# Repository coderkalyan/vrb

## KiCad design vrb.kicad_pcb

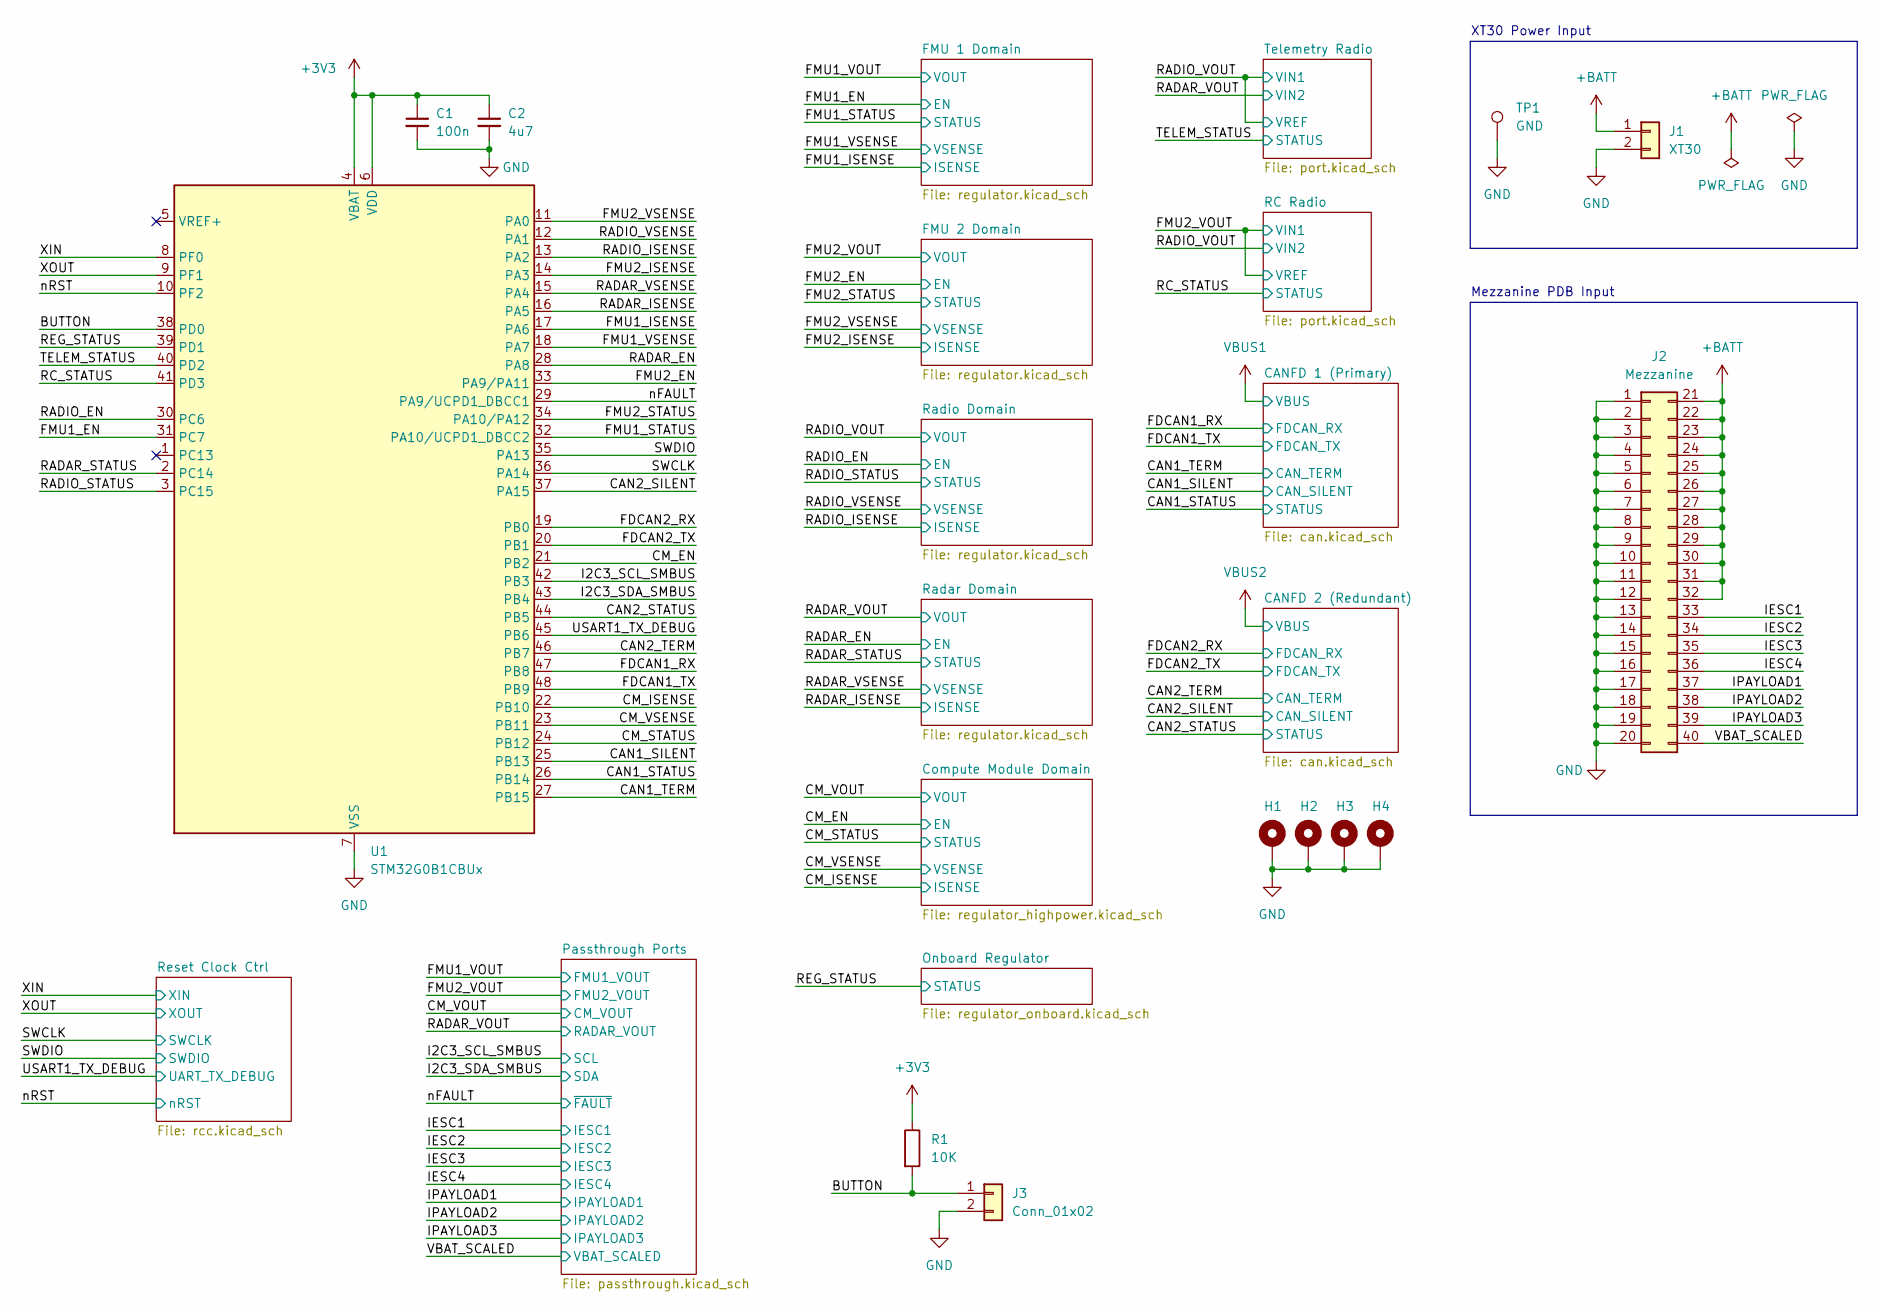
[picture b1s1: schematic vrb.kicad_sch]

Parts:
C1: 100n; C_0402_1005Metric
C2: 4u7; C_0402_1005Metric
H1, H2, H3, H4: MountingHole_Pad; MountingHole_3.2mm_M3_Pad_Via
J1: XT30; AMASS_XT30PW-M_1x02_P2.50mm_Horizontal
J2: Mezzanine; CON_528850474_MOL
J3: Conn_01x02; PinHeader_1x02_P2.54mm_Vertical
R1: 10K; R_0402_1005Metric
TP1: GND; TestPoint_Loop_D2.50mm_Drill1.0mm
U1: STM32G0B1CBUx; QFN-48-1EP_7x7mm_P0.5mm_EP5.6x5.6mm

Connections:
+3V3: C1.1, C2.1, R1.1, U1.4 (VBAT), U1.6 (VDD); also elsewhere on the board
+BATT: J1.1, J2.21, J2.22, J2.23, J2.24, J2.25, J2.26, J2.27, J2.28, J2.29, J2.30, J2.31, J2.32; also elsewhere on the board
/BUTTON: J3.1, R1.2, U1.38 (PD0)
/CAN1_SILENT: U1.25 (PB13); also elsewhere on the board
/CAN1_STATUS: U1.26 (PB14); also elsewhere on the board
/CAN1_TERM: U1.27 (PB15); also elsewhere on the board
/CAN2_SILENT: U1.37 (PA15); also elsewhere on the board
/CAN2_STATUS: U1.44 (PB5); also elsewhere on the board
/CAN2_TERM: U1.46 (PB7); also elsewhere on the board
/CM_EN: U1.21 (PB2); also elsewhere on the board
/CM_ISENSE: U1.22 (PB10); also elsewhere on the board
/CM_STATUS: U1.24 (PB12); also elsewhere on the board
/CM_VSENSE: U1.23 (PB11); also elsewhere on the board
/FDCAN1_RX: U1.47 (PB8); also elsewhere on the board
/FDCAN1_TX: U1.48 (PB9); also elsewhere on the board
/FDCAN2_RX: U1.19 (PB0); also elsewhere on the board
/FDCAN2_TX: U1.20 (PB1); also elsewhere on the board
/FMU1_EN: U1.31 (PC7); also elsewhere on the board
/FMU1_ISENSE: U1.17 (PA6); also elsewhere on the board
/FMU1_STATUS: U1.32 (PA10/UCPD1_DBCC2); also elsewhere on the board
/FMU1_VSENSE: U1.18 (PA7); also elsewhere on the board
/FMU2_EN: U1.33 (PA9/PA11); also elsewhere on the board
/FMU2_ISENSE: U1.14 (PA3); also elsewhere on the board
/FMU2_STATUS: U1.34 (PA10/PA12); also elsewhere on the board
/FMU2_VSENSE: U1.11 (PA0); also elsewhere on the board
/I2C3_SCL_SMBUS: U1.42 (PB3); also elsewhere on the board
/I2C3_SDA_SMBUS: U1.43 (PB4); also elsewhere on the board
/IESC1: J2.33; also elsewhere on the board
/IESC2: J2.34; also elsewhere on the board
/IESC3: J2.35; also elsewhere on the board
/IESC4: J2.36; also elsewhere on the board
/IPAYLOAD1: J2.37; also elsewhere on the board
/IPAYLOAD2: J2.38; also elsewhere on the board
/IPAYLOAD3: J2.39; also elsewhere on the board
/RADAR_EN: U1.28 (PA8); also elsewhere on the board
/RADAR_ISENSE: U1.16 (PA5); also elsewhere on the board
/RADAR_STATUS: U1.2 (PC14); also elsewhere on the board
/RADAR_VSENSE: U1.15 (PA4); also elsewhere on the board
/RADIO_EN: U1.30 (PC6); also elsewhere on the board
/RADIO_ISENSE: U1.13 (PA2); also elsewhere on the board
/RADIO_STATUS: U1.3 (PC15); also elsewhere on the board
/RADIO_VSENSE: U1.12 (PA1); also elsewhere on the board
/RC_STATUS: U1.41 (PD3); also elsewhere on the board
/REG_STATUS: U1.39 (PD1); also elsewhere on the board
/SWCLK: U1.36 (PA14); also elsewhere on the board
/SWDIO: U1.35 (PA13); also elsewhere on the board
/TELEM_STATUS: U1.40 (PD2); also elsewhere on the board
/USART1_TX_DEBUG: U1.45 (PB6); also elsewhere on the board
/VBAT_SCALED: J2.40; also elsewhere on the board
/XIN: U1.8 (PF0); also elsewhere on the board
/XOUT: U1.9 (PF1); also elsewhere on the board
/nFAULT: U1.29 (PA9/UCPD1_DBCC1); also elsewhere on the board
/nRST: U1.10 (PF2); also elsewhere on the board
GND: C1.2, C2.2, H1.1, H2.1, H3.1, H4.1, J1.2, J2.1, J2.2, J2.3, J2.4, J2.5, J2.6, J2.7, J2.8, J2.9, J2.10, J2.11, J2.12, J2.13, J2.14, J2.15, J2.16, J2.17, J2.18, J2.19, J2.20, J3.2, TP1.1, U1.7 (VSS), U1.49 (VSS); also elsewhere on the board

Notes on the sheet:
XT30 Power Input
Mezzanine PDB Input

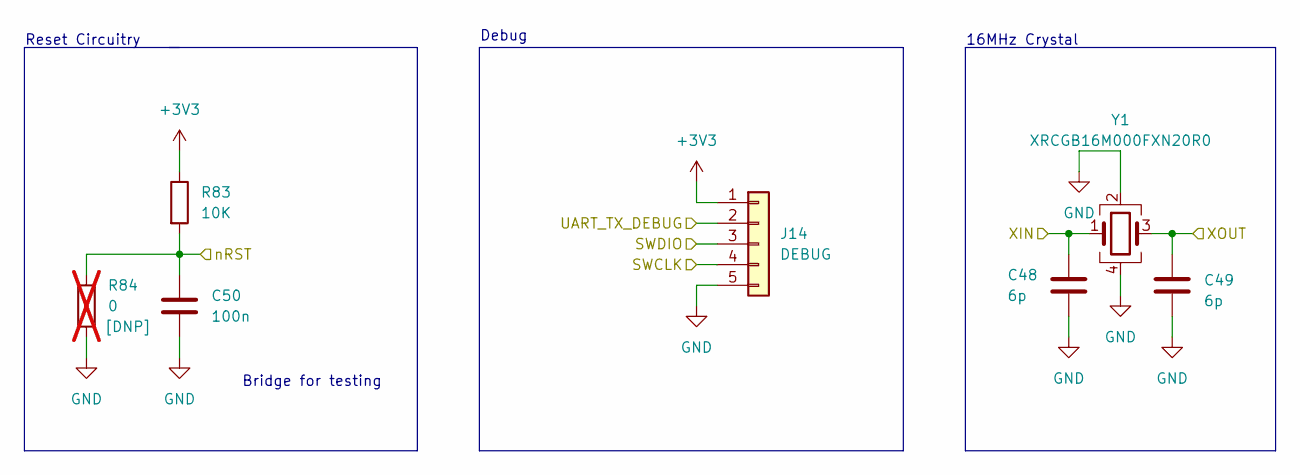
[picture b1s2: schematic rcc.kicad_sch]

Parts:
C48, C49: 6p; C_0402_1005Metric; LCSC C466231
C50: 100n; C_0402_1005Metric; LCSC C907967
J14: DEBUG; PinHeader_1x05_P2.54mm_Vertical
R83: 10K; R_0402_1005Metric; LCSC C102690
R84: 0; R_0402_1005Metric; not fitted
Y1: XRCGB16M000FXN20R0; Crystal_SMD_2016-4Pin_2.0x1.6mm; Part XRCGB16M000FXN20R0; LCSC C907977

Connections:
+3V3: J14.1, R83.1; also elsewhere on the board
/SWCLK: J14.4; also elsewhere on the board
/SWDIO: J14.3; also elsewhere on the board
/USART1_TX_DEBUG: J14.2; also elsewhere on the board
/XIN: C48.1, Y1.1; also elsewhere on the board
/XOUT: C49.1, Y1.3; also elsewhere on the board
/nRST: C50.1, R83.2, R84.1; also elsewhere on the board
GND: C48.2, C49.2, C50.2, J14.5, R84.2, Y1.2, Y1.4; also elsewhere on the board

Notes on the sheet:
Reset Circuitry
Bridge for testing
16MHz Crystal
Debug

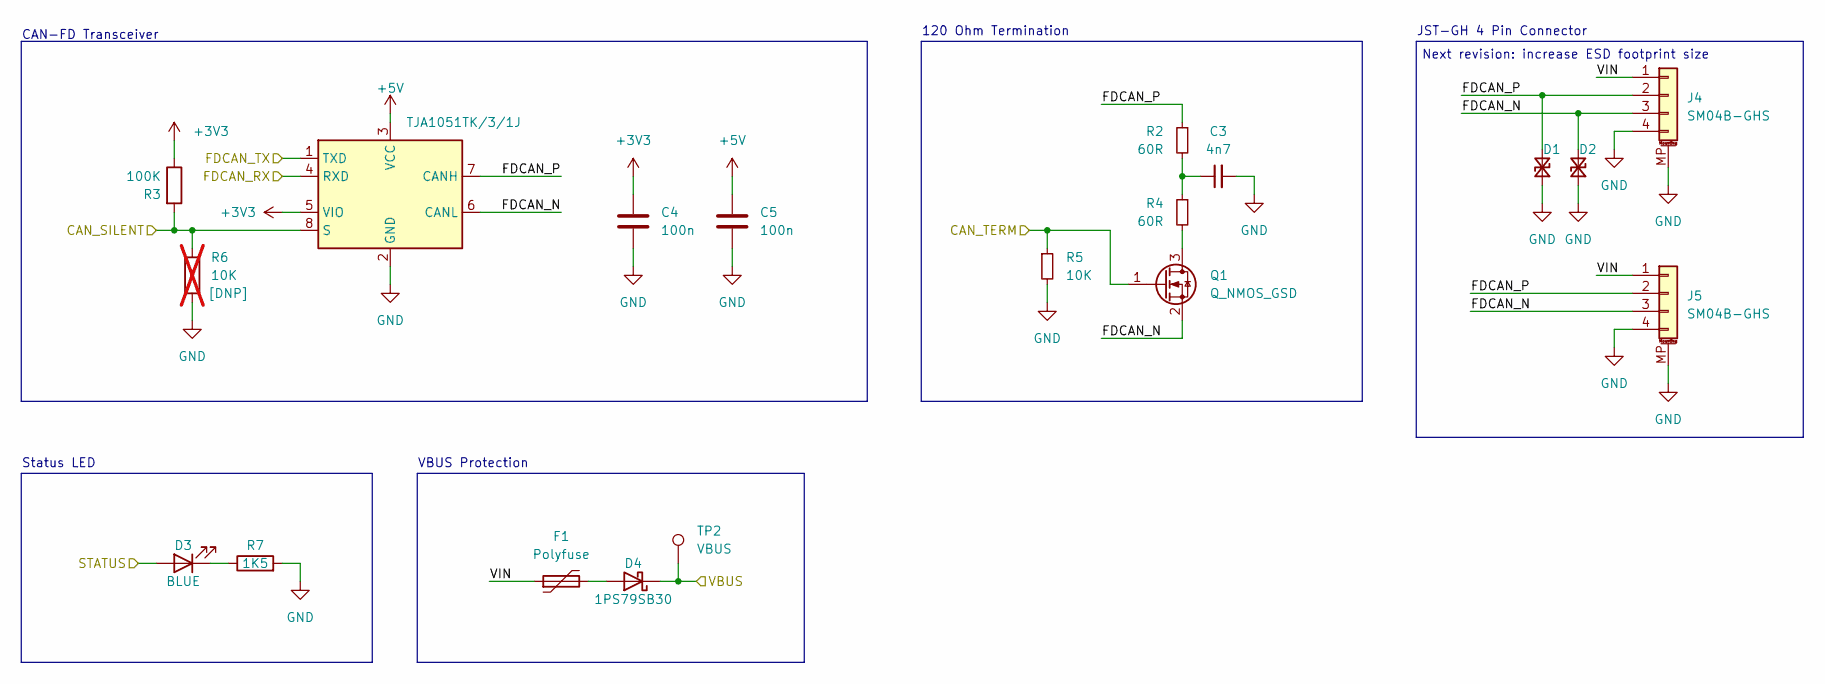
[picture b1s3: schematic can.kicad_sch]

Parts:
C3: 4n7; C_0402_1005Metric
C4, C5: 100n; C_0402_1005Metric
D1, D2: D_TVS_Small; Nexperia_DSN0603-2_0.6x0.3mm_P0.4mm
D3: BLUE; LED_0603_1608Metric
D4: 1PS79SB30; D_SOD-523; LCSC C426690
F1: Polyfuse; Fuse_1206_3216Metric
J4, J5: SM04B-GHS; JST_GH_SM04B-GHS-TB_1x04-1MP_P1.25mm_Horizontal
Q1: Q_NMOS_GSD; SOT-23-3
R2, R4: 60R; R_0402_1005Metric
R3: 100K; R_0402_1005Metric
R5: 10K; R_0402_1005Metric
R6: 10K; R_0402_1005Metric; not fitted
R7: 1K5; R_0402_1005Metric
TP2: VBUS; TestPoint_Pad_1.0x1.0mm
U2: TJA1051TK/3/1J; HVSON-8-1EP_3x3mm_P0.65mm_EP1.6x2.4mm

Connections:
+3V3: C4.1, R3.1, U2.5 (VIO); also elsewhere on the board
+5V: C5.1, U2.3 (VCC); also elsewhere on the board
/CAN2_SILENT: R3.2, R6.1, U2.8 (S); also elsewhere on the board
/CAN2_STATUS: D3.2 (A); also elsewhere on the board
/CAN2_TERM: Q1.1 (G), R5.1; also elsewhere on the board
/CANFD 2 (Redundant)/FDCAN_N: D2.2 (A2), J4.3, J5.3, Q1.2 (S), U2.6 (CANL)
/CANFD 2 (Redundant)/FDCAN_P: D1.2 (A2), J4.2, J5.2, R2.1, U2.7 (CANH)
/CANFD 2 (Redundant)/VIN: F1.1, J4.1, J5.1
/FDCAN2_RX: U2.4 (RXD); also elsewhere on the board
/FDCAN2_TX: U2.1 (TXD); also elsewhere on the board
GND: C3.2, C4.2, C5.2, D1.1 (A1), D2.1 (A1), J4.4, J4.MP (MountPin), J5.4, J5.MP (MountPin), R5.2, R6.2, R7.2, U2.2 (GND), U2.9 (GND); also elsewhere on the board
unnamed: C3.1, R2.2, R4.1
unnamed: D3.1 (K), R7.1
unnamed: D4.2 (A), F1.2
unnamed: Q1.3 (D), R4.2
VBUS2: D4.1 (K), TP2.1; also elsewhere on the board

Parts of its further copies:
C31: 4n7; C_0402_1005Metric
C32, C33: 100n; C_0402_1005Metric
D9, D10: D_TVS_Small; Nexperia_DSN0603-2_0.6x0.3mm_P0.4mm
D11: BLUE; LED_0603_1608Metric
D12: 1PS79SB30; D_SOD-523; LCSC C426690
F6: Polyfuse; Fuse_1206_3216Metric
J6, J7: SM04B-GHS; JST_GH_SM04B-GHS-TB_1x04-1MP_P1.25mm_Horizontal
Q2: Q_NMOS_GSD; SOT-23-3
R40, R42: 60R; R_0402_1005Metric
R41: 100K; R_0402_1005Metric
R45: 10K; R_0402_1005Metric
R46: 10K; R_0402_1005Metric; not fitted
R49: 1K5; R_0402_1005Metric
TP7: VBUS; TestPoint_Pad_1.0x1.0mm
U11: TJA1051TK/3/1J; HVSON-8-1EP_3x3mm_P0.65mm_EP1.6x2.4mm

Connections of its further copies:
+3V3: C32.1, R41.1, U11.5 (VIO); also elsewhere on the board
+5V: C33.1, U11.3 (VCC); also elsewhere on the board
/CAN1_SILENT: R41.2, R46.1, U11.8 (S); also elsewhere on the board
/CAN1_STATUS: D11.2 (A); also elsewhere on the board
/CAN1_TERM: Q2.1 (G), R45.1; also elsewhere on the board
/CANFD 1 (Primary)/FDCAN_N: D10.2 (A2), J6.3, J7.3, Q2.2 (S), U11.6 (CANL)
/CANFD 1 (Primary)/FDCAN_P: D9.2 (A2), J6.2, J7.2, R40.1, U11.7 (CANH)
/CANFD 1 (Primary)/VIN: F6.1, J6.1, J7.1
/FDCAN1_RX: U11.4 (RXD); also elsewhere on the board
/FDCAN1_TX: U11.1 (TXD); also elsewhere on the board
GND: C31.2, C32.2, C33.2, D9.1 (A1), D10.1 (A1), J6.4, J6.MP (MountPin), J7.4, J7.MP (MountPin), R45.2, R46.2, R49.2, U11.2 (GND), U11.9 (GND); also elsewhere on the board
unnamed: C31.1, R40.2, R42.1
unnamed: D11.1 (K), R49.1
unnamed: D12.2 (A), F6.2
unnamed: Q2.3 (D), R42.2
VBUS1: D12.1 (K), TP7.1; also elsewhere on the board

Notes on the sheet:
CAN-FD Transceiver
Next revision: increase ESD footprint size
JST-GH 4 Pin Connector
Status LED
VBUS Protection
120 Ohm Termination

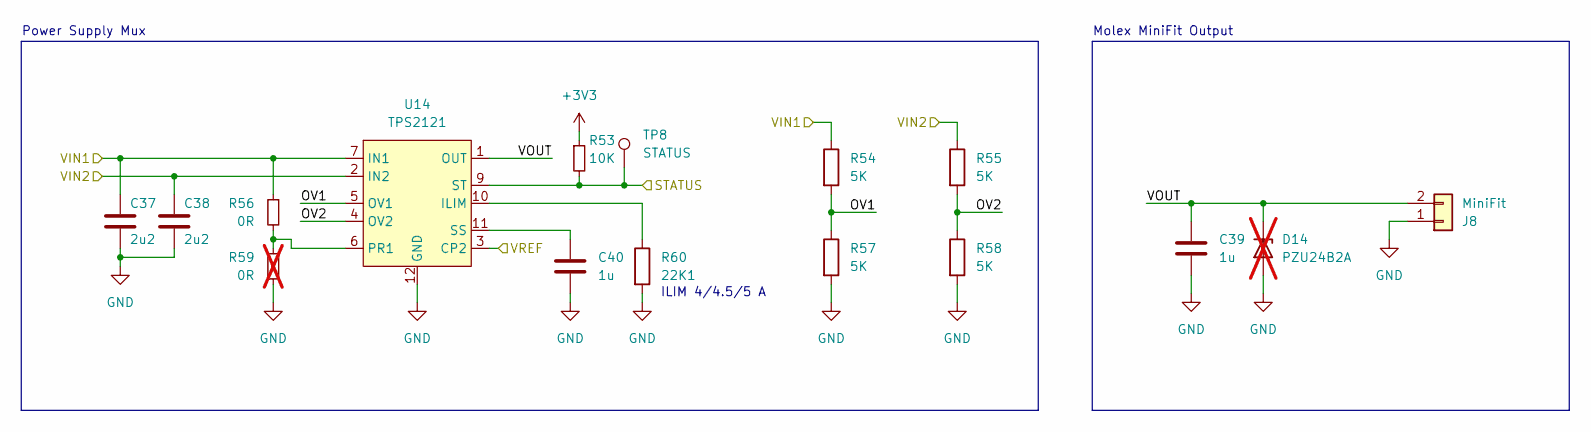
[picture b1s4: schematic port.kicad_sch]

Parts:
C37, C38: 2u2; C_0603_1608Metric
C39, C40: 1u; C_0603_1608Metric
D14: PZU24B2A; D_SOD-323F; not fitted
J8: MiniFit; Molex_Mini-Fit_Jr_5569-02A2_2x01_P4.20mm_Horizontal
R53: 10K; R_0402_1005Metric
R54, R55: 5K; R_0603_1608Metric
R56: 0R; R_0603_1608Metric
R57, R58: 5K; R_0402_1005Metric
R59: 0R; R_0402_1005Metric; not fitted
R60: 22K1; R_0603_1608Metric
TP8: STATUS; TestPoint_Pad_1.0x1.0mm
U14: TPS2121; Texas_VQFN-HR-12_2x2.5mm_P0.5mm

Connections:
+3V3: R53.1; also elsewhere on the board
/FMU2_VOUT: C37.1, R54.1, R56.1, U14.3 (CP2), U14.7 (IN1); also elsewhere on the board
/RADIO_VOUT: C38.1, R55.1, U14.2 (IN2); also elsewhere on the board
/RC Radio/OV1: R54.2, R57.1, U14.5 (OV1)
/RC Radio/OV2: R55.2, R58.1, U14.4 (OV2)
/RC Radio/VOUT: C39.1, D14.1 (K), J8.2, U14.1 (OUT), U14.8 (OUT)
/RC_STATUS: R53.2, TP8.1, U14.9 (ST); also elsewhere on the board
GND: C37.2, C38.2, C39.2, C40.2, D14.2 (A), J8.1, R57.2, R58.2, R59.2, R60.2, U14.12 (GND); also elsewhere on the board
unnamed: R60.1, U14.10 (ILIM)
unnamed: R56.2, R59.1, U14.6 (PR1)
unnamed: C40.1, U14.11 (SS)

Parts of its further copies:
C41, C42: 2u2; C_0603_1608Metric
C43, C44: 1u; C_0603_1608Metric
D15: PZU24B2A; D_SOD-323F; not fitted
J9: MiniFit; Molex_Mini-Fit_Jr_5569-02A2_2x01_P4.20mm_Horizontal
R61: 10K; R_0402_1005Metric
R62, R63: 5K; R_0603_1608Metric
R64: 0R; R_0603_1608Metric
R65, R66: 5K; R_0402_1005Metric
R67: 0R; R_0402_1005Metric; not fitted
R68: 22K1; R_0603_1608Metric
TP9: STATUS; TestPoint_Pad_1.0x1.0mm
U15: TPS2121; Texas_VQFN-HR-12_2x2.5mm_P0.5mm

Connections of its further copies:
+3V3: R61.1; also elsewhere on the board
/RADAR_VOUT: C42.1, R63.1, U15.2 (IN2); also elsewhere on the board
/RADIO_VOUT: C41.1, R62.1, R64.1, U15.3 (CP2), U15.7 (IN1); also elsewhere on the board
/TELEM_STATUS: R61.2, TP9.1, U15.9 (ST); also elsewhere on the board
/Telemetry Radio/OV1: R62.2, R65.1, U15.5 (OV1)
/Telemetry Radio/OV2: R63.2, R66.1, U15.4 (OV2)
/Telemetry Radio/VOUT: C43.1, D15.1 (K), J9.2, U15.1 (OUT), U15.8 (OUT)
GND: C41.2, C42.2, C43.2, C44.2, D15.2 (A), J9.1, R65.2, R66.2, R67.2, R68.2, U15.12 (GND); also elsewhere on the board
unnamed: R68.1, U15.10 (ILIM)
unnamed: R64.2, R67.1, U15.6 (PR1)
unnamed: C44.1, U15.11 (SS)

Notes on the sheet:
Molex MiniFit Output
Power Supply Mux
ILIM 4/4.5/5 A

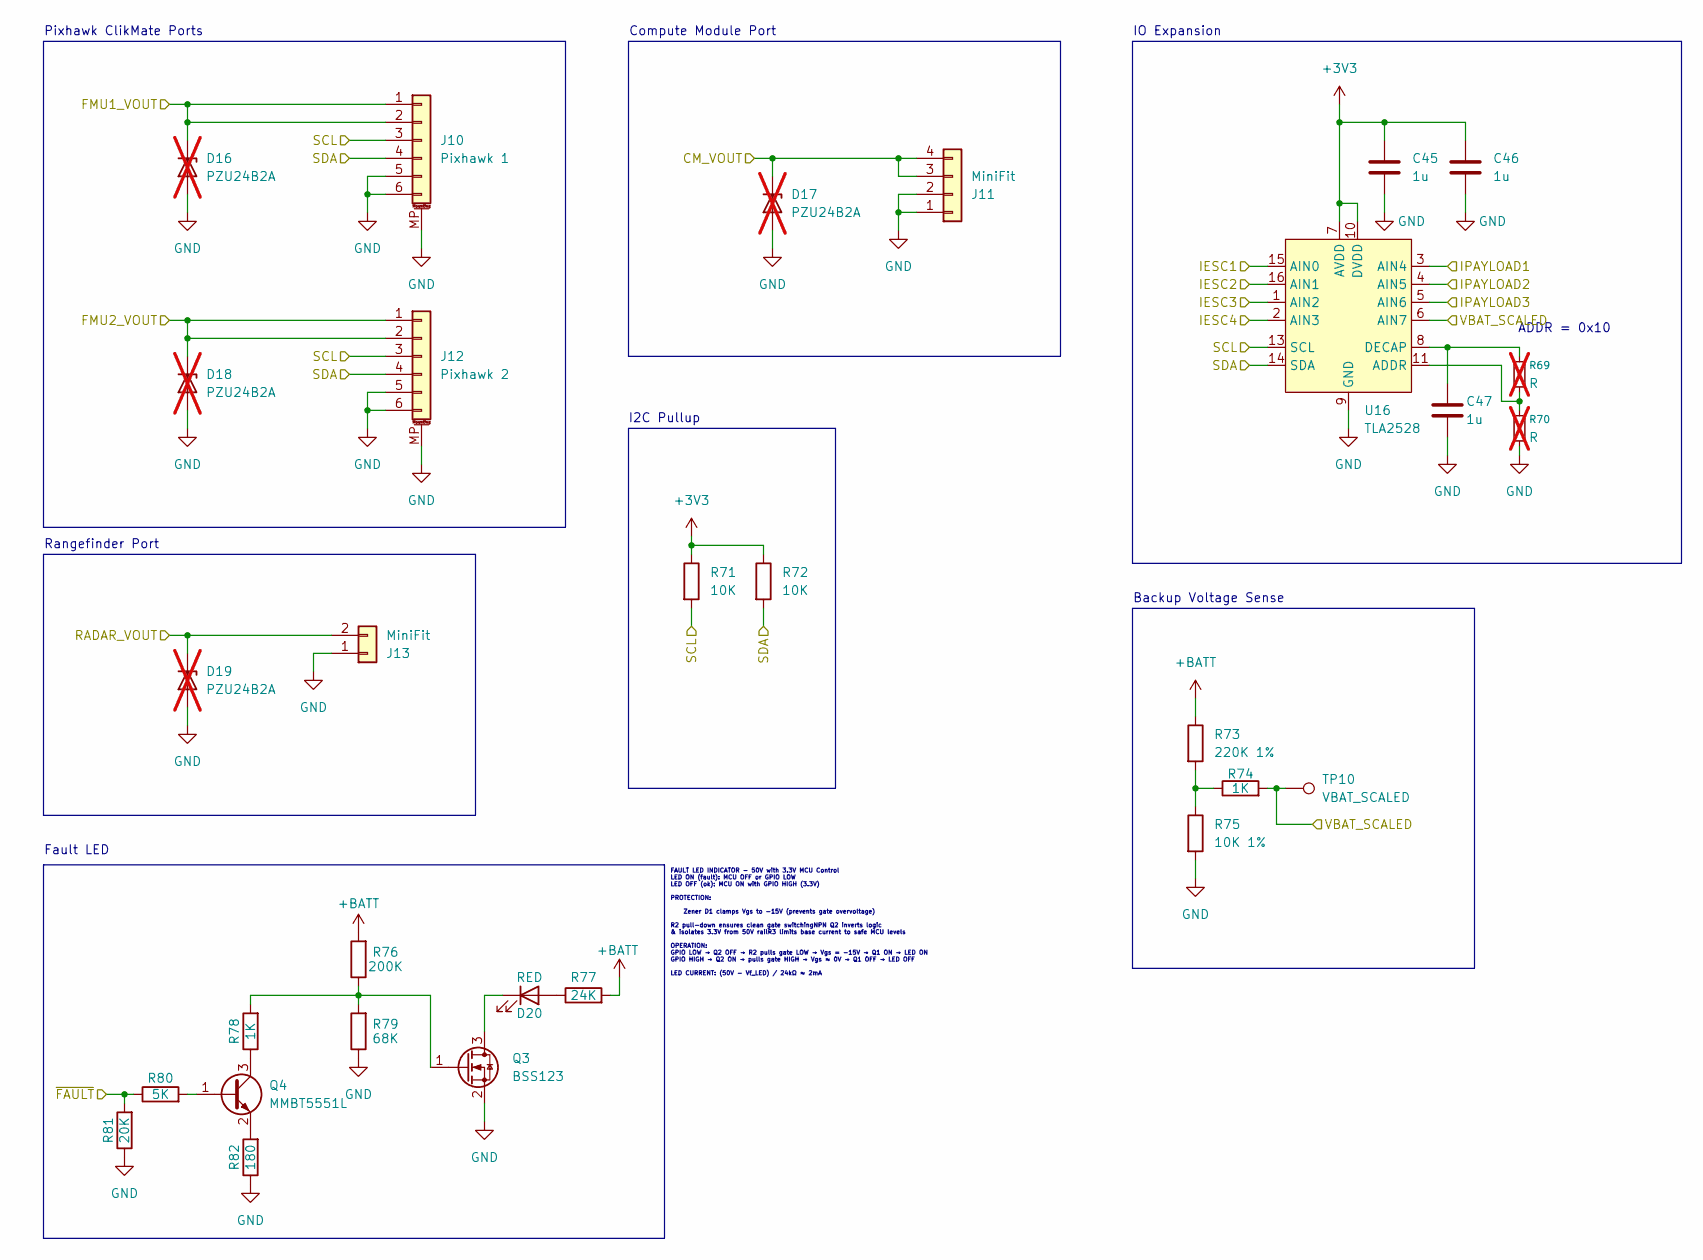
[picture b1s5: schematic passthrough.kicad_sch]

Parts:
C45, C46, C47: 1u; C_0402_1005Metric
D16, D17, D18, D19: PZU24B2A; D_SOD-323F; not fitted
D20: RED; LED_0603_1608Metric
J10: Pixhawk 1; Molex_CLIK-Mate_502494-0670_1x06-1MP_P2.00mm_Horizontal
J11: MiniFit; Molex_Mini-Fit_Jr_5569-04A2_2x02_P4.20mm_Horizontal
J12: Pixhawk 2; Molex_CLIK-Mate_502494-0670_1x06-1MP_P2.00mm_Horizontal
J13: MiniFit; Molex_Mini-Fit_Jr_5569-02A2_2x01_P4.20mm_Horizontal
Q3: BSS123; SOT-23
Q4: MMBT5551L; SOT-23
R69, R70: R; R_0402_1005Metric; not fitted
R71, R72: 10K; R_0402_1005Metric
R73: 220K 1%; R_0603_1608Metric
R74: 1K; R_0603_1608Metric
R75: 10K 1%; R_0603_1608Metric
R76: 200K; R_0402_1005Metric
R77: 24K; R_0402_1005Metric
R78: 1K; R_0402_1005Metric
R79: 68K; R_0402_1005Metric
R80: 5K; R_0402_1005Metric
R81: 20K; R_0402_1005Metric
R82: 180; R_0402_1005Metric
TP10: VBAT_SCALED; TestPoint_Pad_1.5x1.5mm
U16: TLA2528; WQFN-16-1EP_3x3mm_P0.5mm_EP1.68x1.68mm

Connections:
+3V3: C45.1, C46.1, R71.1, R72.1, U16.7 (AVDD), U16.10 (DVDD); also elsewhere on the board
+BATT: R73.1, R76.2, R77.2; also elsewhere on the board
/CM_VOUT: D17.1 (K), J11.3, J11.4; also elsewhere on the board
/FMU1_VOUT: D16.1 (K), J10.1, J10.2; also elsewhere on the board
/FMU2_VOUT: D18.1 (K), J12.1, J12.2; also elsewhere on the board
/I2C3_SCL_SMBUS: J10.3, J12.3, R71.2, U16.13 (SCL); also elsewhere on the board
/I2C3_SDA_SMBUS: J10.4, J12.4, R72.2, U16.14 (SDA); also elsewhere on the board
/IESC1: U16.15 (AIN0); also elsewhere on the board
/IESC2: U16.16 (AIN1); also elsewhere on the board
/IESC3: U16.1 (AIN2); also elsewhere on the board
/IESC4: U16.2 (AIN3); also elsewhere on the board
/IPAYLOAD1: U16.3 (AIN4); also elsewhere on the board
/IPAYLOAD2: U16.4 (AIN5); also elsewhere on the board
/IPAYLOAD3: U16.5 (AIN6); also elsewhere on the board
/RADAR_VOUT: D19.1 (K), J13.2; also elsewhere on the board
/VBAT_SCALED: R74.2, TP10.1, U16.6 (AIN7); also elsewhere on the board
/nFAULT: R80.1, R81.2; also elsewhere on the board
GND: C45.2, C46.2, C47.2, D16.2 (A), D17.2 (A), D18.2 (A), D19.2 (A), J10.5, J10.6, J10.MP (MountPin), J11.1, J11.2, J12.5, J12.6, J12.MP (MountPin), J13.1, Q3.2 (S), R70.2, R75.2, R79.1, R81.1, R82.1, U16.9 (GND), U16.17 (GND); also elsewhere on the board
unnamed: D20.2 (A), R77.1
unnamed: D20.1 (K), Q3.3 (D)
unnamed: Q3.1 (G), R76.1, R78.2, R79.2
unnamed: Q4.1 (B), R80.2
unnamed: Q4.3 (C), R78.1
unnamed: Q4.2 (E), R82.2
unnamed: R73.2, R74.1, R75.1
unnamed: R69.2, R70.1, U16.11 (ADDR)
unnamed: C47.1, R69.1, U16.8 (DECAP)

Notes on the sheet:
Fault LED
Pixhawk ClikMate Ports
I2C Pullup
Rangefinder Port
Backup Voltage Sense
FAULT LED INDICATOR - 50V with 3.3V MCU Control LED ON (fault): MCU OFF or GPIO LOW LED OFF (ok): MCU ON with GPIO HIGH (3.3V) PROTECTION: Zener D1 clamps Vgs to -15V (prevents gate overvoltage) R2 pull-down ensures clean gate switchingNPN Q2 inverts logic & isolates 3.3V from 50V railR3 limits bas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
ADDR = 0x10
Compute Module Port
IO Expansion

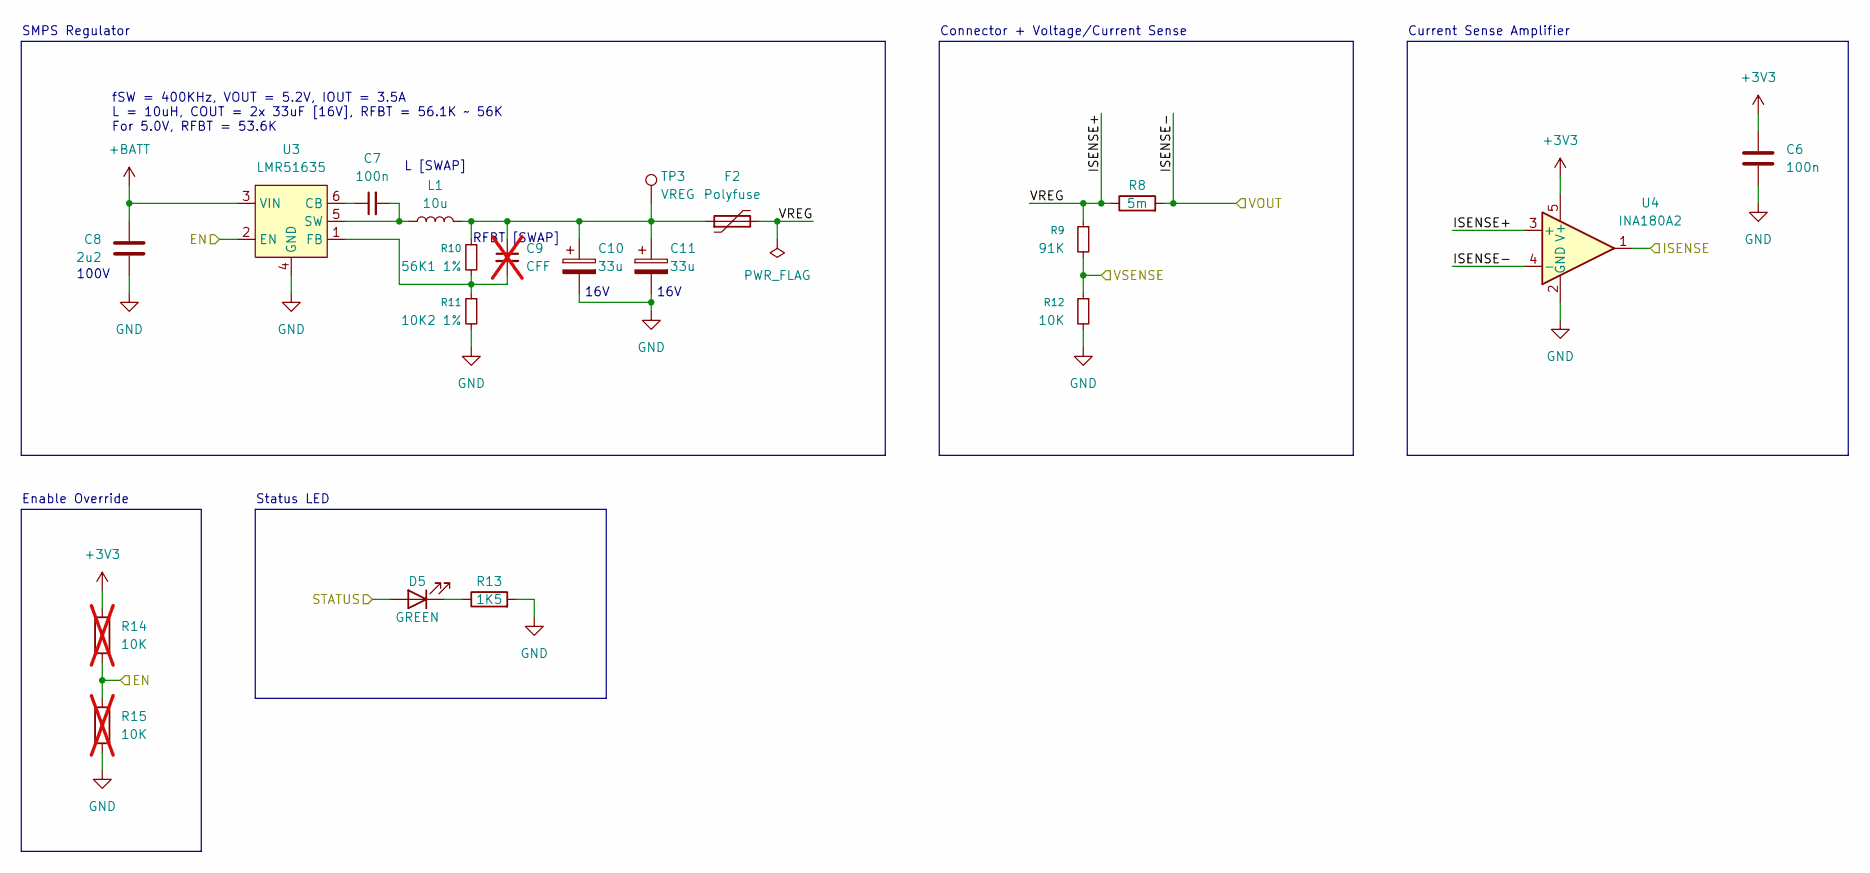
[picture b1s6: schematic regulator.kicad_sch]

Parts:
C6: 100n; C_0402_1005Metric
C7: 100n; C_0805_2012Metric
C8: 2u2; C_1206_3216Metric
C9: CFF; C_0805_2012Metric; not fitted
C10, C11: 33u; CP_EIA-3528-12_Kemet-T
D5: GREEN; LED_0603_1608Metric
F2: Polyfuse; Fuse_1206_3216Metric
L1: 10u; L_Bourns_SRP7028A_7.3x6.6mm
R8: 5m; R_1206_3216Metric
R9: 91K; R_0402_1005Metric
R10: 56K1 1%; R_0603_1608Metric
R11: 10K2 1%; R_0603_1608Metric
R12: 10K; R_0402_1005Metric
R13: 1K5; R_0402_1005Metric
R14, R15: 10K; R_0603_1608Metric; not fitted
TP3: VREG; TestPoint_Pad_2.0x2.0mm
U3: LMR51635; SOT-23-6
U4: INA180A2; SOT-23-5

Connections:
+3V3: C6.1, R14.1, U4.5 (V+); also elsewhere on the board
+BATT: C8.1, U3.3 (VIN); also elsewhere on the board
/FMU1_EN: R14.2, R15.1, U3.2 (EN); also elsewhere on the board
/FMU1_ISENSE: U4.1; also elsewhere on the board
/FMU1_STATUS: D5.2 (A); also elsewhere on the board
/FMU1_VOUT: R8.2, U4.4 (-); also elsewhere on the board
/FMU1_VSENSE: R9.2, R12.1; also elsewhere on the board
/FMU 1 Domain/ISENSE+: F2.2, R8.1, R9.1, U4.3 (+)
GND: C6.2, C8.2, C10.2, C11.2, R11.2, R12.2, R13.2, R15.2, U3.4 (GND), U4.2 (GND); also elsewhere on the board
unnamed: C9.1, C10.1, C11.1, F2.1, L1.2, R10.1, TP3.1
unnamed: D5.1 (K), R13.1
unnamed: C7.1, U3.6 (CB)
unnamed: C9.2, R10.2, R11.1, U3.1 (FB)
unnamed: C7.2, L1.1, U3.5 (SW)

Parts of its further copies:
C12, C18, C24: 100n; C_0402_1005Metric
C13, C19, C25: 100n; C_0805_2012Metric
C14, C20, C26: 2u2; C_1206_3216Metric
C15, C21, C27: CFF; C_0805_2012Metric; not fitted
C16, C17, C22, C23, C28, C29: 33u; CP_EIA-3528-12_Kemet-T
D6, D7, D8: GREEN; LED_0603_1608Metric
F3, F4, F5: Polyfuse; Fuse_1206_3216Metric
L2, L3, L4: 10u; L_Bourns_SRP7028A_7.3x6.6mm
R16, R24, R32: 5m; R_1206_3216Metric
R17, R25, R33: 91K; R_0402_1005Metric
R18, R26, R34: 56K1 1%; R_0603_1608Metric
R19, R27, R35: 10K2 1%; R_0603_1608Metric
R20, R28, R36: 10K; R_0402_1005Metric
R21, R29, R37: 1K5; R_0402_1005Metric
R22, R23, R30, R31, R38, R39: 10K; R_0603_1608Metric; not fitted
TP4, TP5, TP6: VREG; TestPoint_Pad_2.0x2.0mm
U5, U7, U9: LMR51635; SOT-23-6
U6, U8, U10: INA180A2; SOT-23-5

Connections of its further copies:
+3V3: C12.1, C18.1, C24.1, R22.1, R30.1, R38.1, U6.5 (V+), U8.5 (V+), U10.5 (V+); also elsewhere on the board
+BATT: C14.1, C20.1, C26.1, U5.3 (VIN), U7.3 (VIN), U9.3 (VIN); also elsewhere on the board
/FMU2_EN: R22.2, R23.1, U5.2 (EN); also elsewhere on the board
/FMU2_ISENSE: U6.1; also elsewhere on the board
/FMU2_STATUS: D6.2 (A); also elsewhere on the board
/FMU2_VOUT: R16.2, U6.4 (-); also elsewhere on the board
/FMU2_VSENSE: R17.2, R20.1; also elsewhere on the board
/FMU 2 Domain/ISENSE+: F3.2, R16.1, R17.1, U6.3 (+)
/RADAR_EN: R38.2, R39.1, U9.2 (EN); also elsewhere on the board
/RADAR_ISENSE: U10.1; also elsewhere on the board
/RADAR_STATUS: D8.2 (A); also elsewhere on the board
/RADAR_VOUT: R32.2, U10.4 (-); also elsewhere on the board
/RADAR_VSENSE: R33.2, R36.1; also elsewhere on the board
/RADIO_EN: R30.2, R31.1, U7.2 (EN); also elsewhere on the board
/RADIO_ISENSE: U8.1; also elsewhere on the board
/RADIO_STATUS: D7.2 (A); also elsewhere on the board
/RADIO_VOUT: R24.2, U8.4 (-); also elsewhere on the board
/RADIO_VSENSE: R25.2, R28.1; also elsewhere on the board
/Radar Domain/ISENSE+: F5.2, R32.1, R33.1, U10.3 (+)
/Radio Domain/ISENSE+: F4.2, R24.1, R25.1, U8.3 (+)
GND: C12.2, C14.2, C16.2, C17.2, C18.2, C20.2, C22.2, C23.2, C24.2, C26.2, C28.2, C29.2, R19.2, R20.2, R21.2, R23.2, R27.2, R28.2, R29.2, R31.2, R35.2, R36.2, R37.2, R39.2, U5.4 (GND), U6.2 (GND), U7.4 (GND), U8.2 (GND), U9.4 (GND), U10.2 (GND); also elsewhere on the board
unnamed: C15.1, C16.1, C17.1, F3.1, L2.2, R18.1, TP4.1
unnamed: C21.1, C22.1, C23.1, F4.1, L3.2, R26.1, TP5.1
unnamed: C27.1, C28.1, C29.1, F5.1, L4.2, R34.1, TP6.1
unnamed: D6.1 (K), R21.1
unnamed: D7.1 (K), R29.1
unnamed: D8.1 (K), R37.1
unnamed: C13.1, U5.6 (CB)
unnamed: C15.2, R18.2, R19.1, U5.1 (FB)
unnamed: C13.2, L2.1, U5.5 (SW)
unnamed: C19.1, U7.6 (CB)
unnamed: C21.2, R26.2, R27.1, U7.1 (FB)
unnamed: C19.2, L3.1, U7.5 (SW)
unnamed: C25.1, U9.6 (CB)
unnamed: C27.2, R34.2, R35.1, U9.1 (FB)
unnamed: C25.2, L4.1, U9.5 (SW)

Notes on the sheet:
Enable Override
16V
Status LED
Current Sense Amplifier
L [SWAP]
RFBT [SWAP]
SMPS Regulator
Connector + Voltage/Current Sense
fSW = 400KHz, VOUT = 5.2V, IOUT = 3.5A L = 10uH, COUT = 2x 33uF [16V], RFBT = 56.1K ~ 56K For 5.0V, RFBT = 53.6K
100V

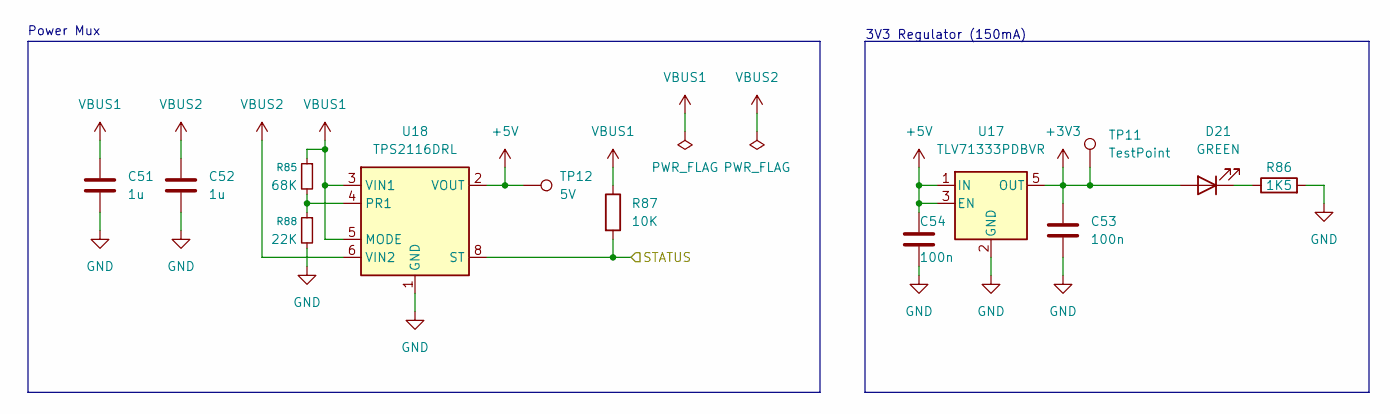
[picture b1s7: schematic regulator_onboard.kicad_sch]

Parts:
C51, C52: 1u; C_0603_1608Metric
C53, C54: 100n; C_0603_1608Metric; LCSC C282519
D21: GREEN; LED_0603_1608Metric; Part QBLP595-IG; LCSC C2856703
R85: 68K; R_0402_1005Metric
R86: 1K5; R_0402_1005Metric; LCSC C25930
R87: 10K; R_0402_1005Metric
R88: 22K; R_0402_1005Metric
TP11: TestPoint; TestPoint_Pad_1.0x1.0mm
TP12: 5V; TestPoint_Pad_1.0x1.0mm
U17: TLV71333PDBVR; SOT-23-5; LCSC C2867340
U18: TPS2116DRL; SOT-583-8

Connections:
+3V3: C53.1, D21.2 (A), TP11.1, U17.5 (OUT); also elsewhere on the board
+5V: C54.1, TP12.1, U17.1 (IN), U17.3 (EN), U18.2 (VOUT), U18.7 (VOUT); also elsewhere on the board
/REG_STATUS: R87.2, U18.8 (ST); also elsewhere on the board
GND: C51.2, C52.2, C53.2, C54.2, R86.2, R88.2, U17.2 (GND), U18.1 (GND); also elsewhere on the board
unnamed: D21.1 (K), R86.1
unnamed: R85.2, R88.1, U18.4 (PR1)
VBUS1: C51.1, R85.1, R87.1, U18.3 (VIN1), U18.5 (MODE); also elsewhere on the board
VBUS2: C52.1, U18.6 (VIN2); also elsewhere on the board

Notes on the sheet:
3V3 Regulator (150mA)
Power Mux

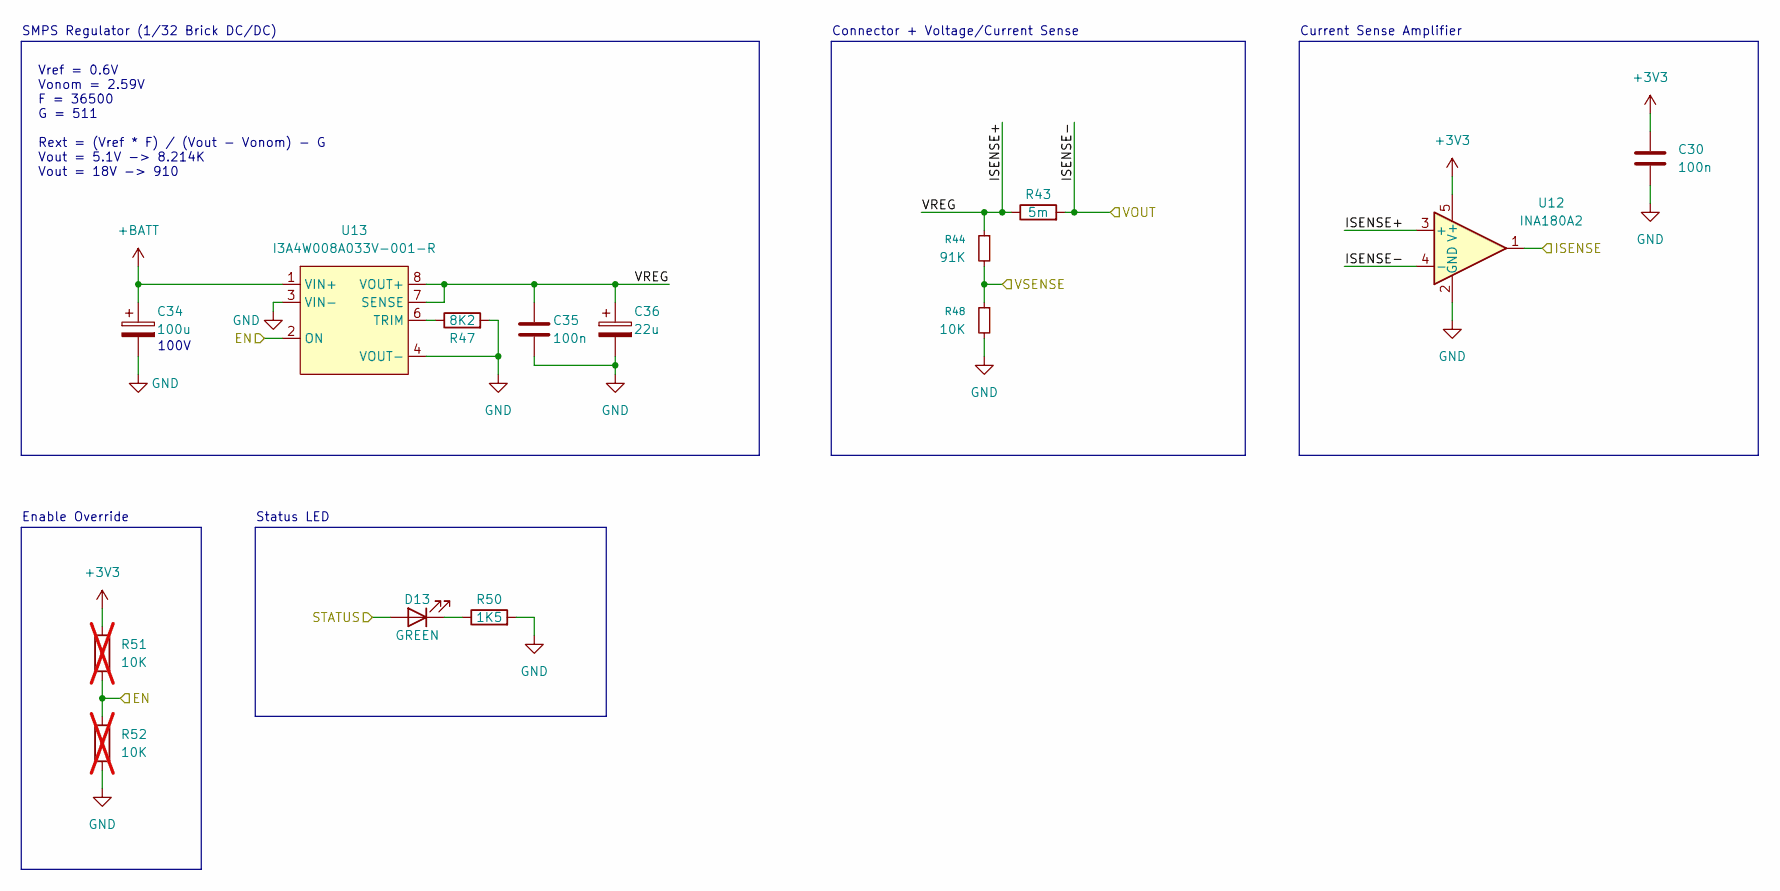
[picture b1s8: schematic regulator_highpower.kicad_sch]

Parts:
C30: 100n; C_0402_1005Metric
C34: 100u; C_1206_3216Metric
C35: 100n; C_0805_2012Metric
C36: 22u; C_0805_2012Metric
D13: GREEN; LED_0603_1608Metric
R43: 5m; R_1206_3216Metric
R44: 91K; R_0402_1005Metric
R47: 8K2; R_0603_1608Metric
R48: 10K; R_0603_1608Metric
R50: 1K5; R_0402_1005Metric
R51, R52: 10K; R_0603_1608Metric; not fitted
U12: INA180A2; SOT-23-5
U13: I3A4W008A033V-001-R; CONV_I3A4W008A033V-001-R

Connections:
+3V3: C30.1, R51.1, U12.5 (V+); also elsewhere on the board
+BATT: C34.1, U13.1 (VIN+); also elsewhere on the board
/CM_EN: R51.2, R52.1, U13.2 (ON); also elsewhere on the board
/CM_ISENSE: U12.1; also elsewhere on the board
/CM_STATUS: D13.2 (A); also elsewhere on the board
/CM_VOUT: R43.2, U12.4 (-); also elsewhere on the board
/CM_VSENSE: R44.2, R48.1; also elsewhere on the board
/Compute Module Domain/ISENSE+: C35.1, C36.1, R43.1, R44.1, U12.3 (+), U13.7 (SENSE), U13.8 (VOUT+)
GND: C30.2, C34.2, C35.2, C36.2, R47.2, R48.2, R50.2, R52.2, U12.2 (GND), U13.3 (VIN-), U13.4 (VOUT-); also elsewhere on the board
unnamed: D13.1 (K), R50.1
unnamed: R47.1, U13.6 (TRIM)

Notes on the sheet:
Vref = 0.6V Vonom = 2.59V F = 36500 G = 511 Rext = (Vref * F) / (Vout - Vonom) - G Vout = 5.1V -> 8.214K Vout = 18V -> 910
Enable Override
SMPS Regulator (1/32 Brick DC/DC)
Current Sense Amplifier
Status LED
Connector + Voltage/Current Sense
100V
